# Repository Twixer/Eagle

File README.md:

Eagle projects
- Eagle-Tutorial-1-Files  : tutorial
- led-blink-relay : tutorial
- RFM12B : home automation
- TinyTx3 : home automation

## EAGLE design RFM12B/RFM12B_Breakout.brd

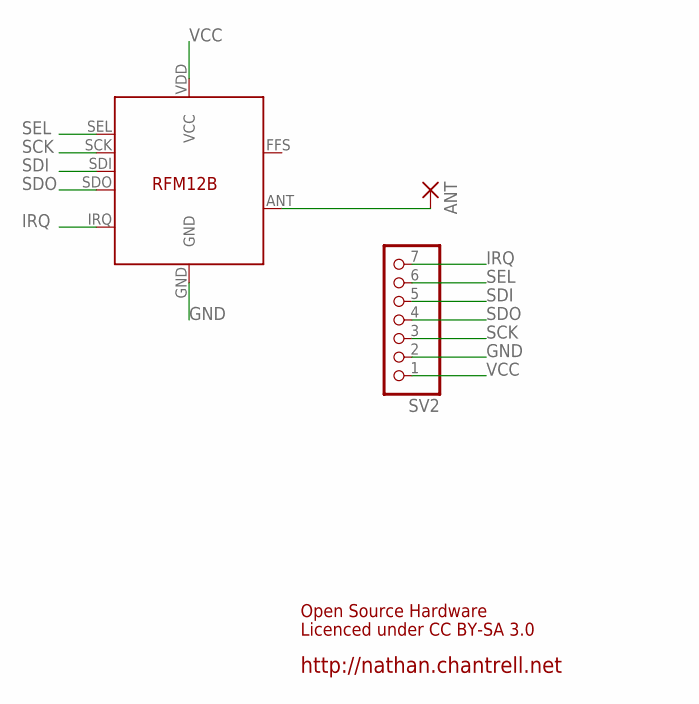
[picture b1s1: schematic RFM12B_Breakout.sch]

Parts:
ANT: 1,6/0,8
SV2: PINHD-1X7; 1X07
U$1: RFM12B

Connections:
GND: SV2.2, U$1.GND
IRQ: SV2.7, U$1.IRQ
unnamed: ANT.1, U$1.ANT
SCK: SV2.3, U$1.SCK
SDI: SV2.5, U$1.SDI
SDO: SV2.4, U$1.SDO
SEL: SV2.6, U$1.SEL
VCC: SV2.1, U$1.VDD (VCC)

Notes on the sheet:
http://nathan.chantrell.net
Open Source Hardware
Licenced under CC BY-SA 3.0

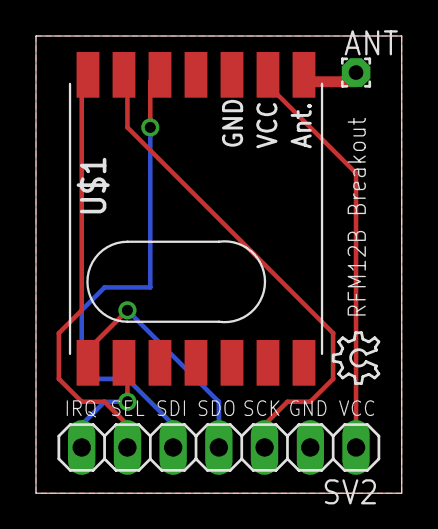
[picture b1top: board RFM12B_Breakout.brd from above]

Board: 2 copper layers, 20.3 x 25.4 mm, 4 parts (0 on the bottom side), 8 nets.

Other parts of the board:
U$4: OSHW_6X100_NOTEXT

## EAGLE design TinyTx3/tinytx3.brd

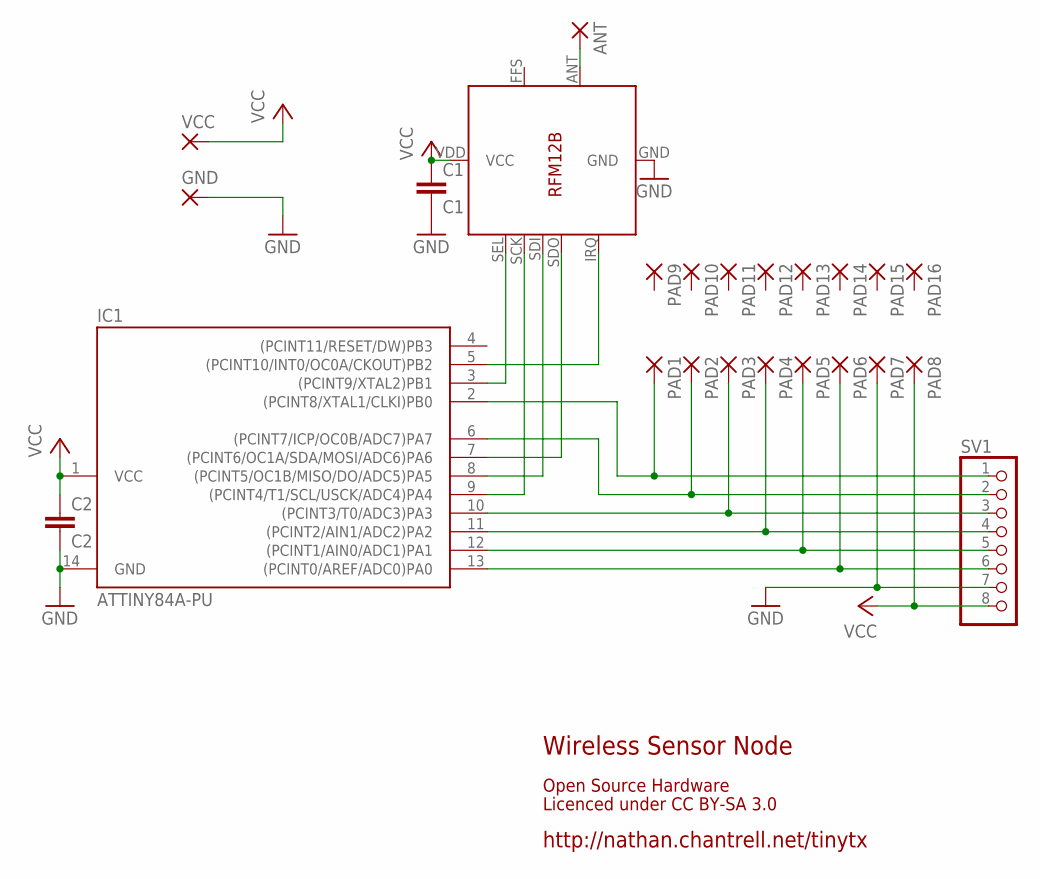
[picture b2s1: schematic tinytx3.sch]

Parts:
ANT: 1,6/0,8
C1: C1; C025-025X050
C2: C2; C025-025X050
GND: 2,15/1,0
IC1: ATTINY84A-PU; DIL14
PAD1, PAD2, PAD3, PAD4, PAD5, PAD6, PAD7, PAD8, PAD9, PAD10, PAD11, PAD12, PAD13, PAD14, PAD15, PAD16: 1,6/0,9
SV1: PINHD-1X8; 1X08
U$1: RFM12B
VCC: 2,15/1,0

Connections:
GND: C1.2, C2.2, GND.1, IC1.14 (GND), PAD7.1, SV1.7, U$1.GND
unnamed: IC1.3 ((PCINT9/XTAL2)PB1), U$1.SEL
unnamed: IC1.5 ((PCINT10/INT0/OC0A/CKOUT)PB2), U$1.IRQ
unnamed: IC1.8 ((PCINT5/OC1B/MISO/DO/ADC5)PA5), U$1.SDI
unnamed: IC1.7 ((PCINT6/OC1A/SDA/MOSI/ADC6)PA6), U$1.SDO
unnamed: ANT.1, U$1.ANT
unnamed: IC1.9 ((PCINT4/T1/SCL/USCK/ADC4)PA4), U$1.SCK
unnamed: IC1.6 ((PCINT7/ICP/OC0B/ADC7)PA7), PAD2.1, SV1.2
unnamed: IC1.13 ((PCINT0/AREF/ADC0)PA0), PAD6.1, SV1.6
unnamed: IC1.12 ((PCINT1/AIN0/ADC1)PA1), PAD5.1, SV1.5
unnamed: IC1.2 ((PCINT8/XTAL1/CLKI)PB0), PAD1.1, SV1.1
unnamed: IC1.11 ((PCINT2/AIN1/ADC2)PA2), PAD4.1, SV1.4
unnamed: IC1.10 ((PCINT3/T0/ADC3)PA3), PAD3.1, SV1.3
VCC: C1.1, C2.1, IC1.1 (VCC), PAD8.1, SV1.8, U$1.VDD (VCC), VCC.1

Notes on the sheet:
http://nathan.chantrell.net/tinytx
Wireless Sensor Node
Licenced under CC BY-SA 3.0
Open Source Hardware

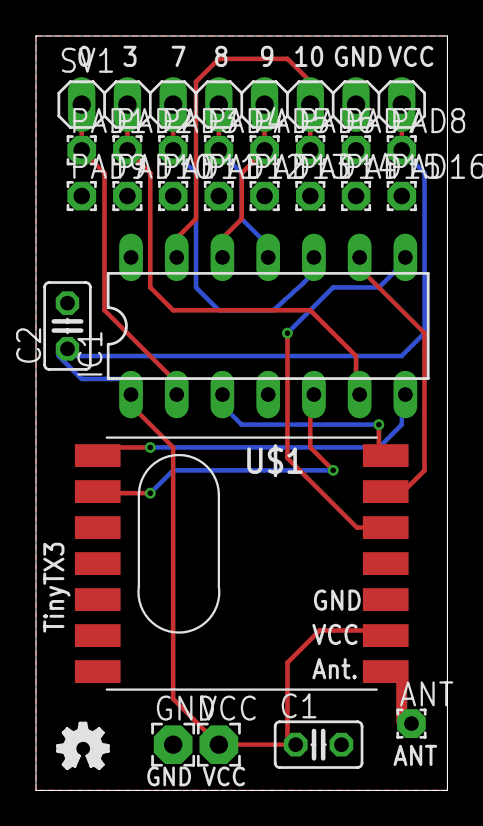
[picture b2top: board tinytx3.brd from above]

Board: 2 copper layers, 22.9 x 41.9 mm, 25 parts (0 on the bottom side), 14 nets.

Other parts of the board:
U$2: OSHW_FILLX100_NOTEXT

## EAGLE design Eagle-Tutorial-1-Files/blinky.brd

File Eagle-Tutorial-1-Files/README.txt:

Jeremy Blum's Eagle CAD Tutorial Series
=======================================
These files are meant to accompany Jeremy Blum's Eagle CAD Tutorial Series.  
These tutorials were sponsored by element14 (http://www.element14.com) with support from CadSoft (http://www.cadsoftusa.com)  
You can watch these tutorials on youtube or my website:  
>>YouTube				- http://www.youtube.com/playlist?list=PL868B73617C6F6FAD  
>>Jeremy's Website		- http://jeremyblum.com/category/eagle-tutorials/  

Open Source License
-------------------
These files are distributed under the GNU GPL Open Source License.  
Further information can be found in the LICENSE file.  

Learn More about Eagle
----------------------
If you need help with Eagle or want to learn more, I recommend these resources:  
>>element14 CadSoft Group	- http://www.element-14.com/cadsoft  
>>Eagle Guided Tour			- http://www.cadsoftusa.com/eagle-pcb-design-software/guided-tour/  
>>Sparkfun Eagle Tutorials	- http://www.sparkfun.com/tutorials/108  

Author Info
-----------
The Original author of these files is Jeremy Blum.  
He can be reached through his website, http://www.jeremyblum.com.  
NO WARRANTY is provided with these files, since they are released under the GNU GPL.  
Follow Jeremy on Twitter: http://www.twitter.com/sciguy14  
Subscribe to Jeremy on Youtube: http://www.youtube.com/subscription_center?add_user=sciguy14  
"Like" Jeremy on Facebook: http://www.facebook.com/JeremyTheEngineer

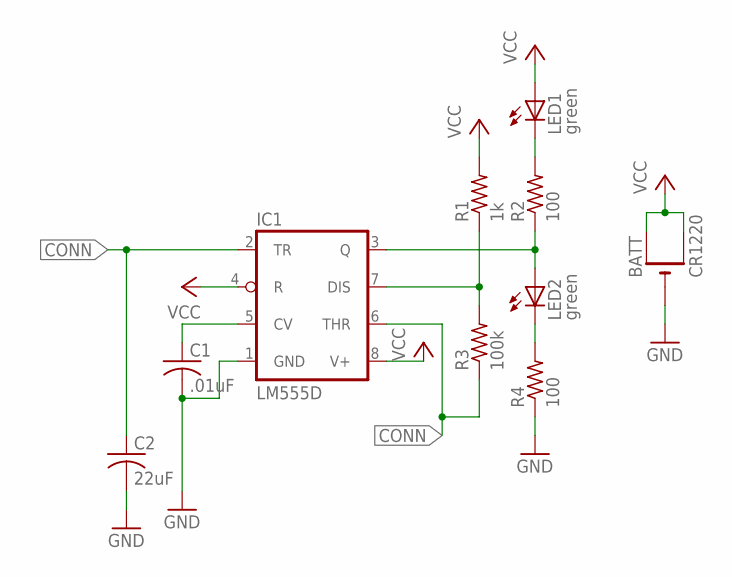
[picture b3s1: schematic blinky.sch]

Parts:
BATT: CR1220; CR1220-SMD
C1: .01uF; C0805
C2: 22uF; C0805
IC1: LM555D; SO08
LED1, LED2: green; CHIPLED_0805
R1: 1k; R0805
R2, R4: 100; R0805
R3: 100k; R0805

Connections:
CONN: C2.1, IC1.2 (TR), IC1.6 (THR), R3.1
GND: BATT.-, C1.2, C2.2, IC1.1 (GND), R4.1
unnamed: LED1.C, R2.2
unnamed: IC1.3 (Q), LED2.A, R2.1
unnamed: LED2.C, R4.2
unnamed: IC1.7 (DIS), R1.1, R3.2
unnamed: C1.1, IC1.5 (CV)
VCC: BATT.+$1 (+), BATT.+$2 (+1), IC1.4 (R), IC1.8 (V+), LED1.A, R1.2

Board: 2 copper layers, 10 parts (0 on the bottom side), 8 nets, no tracks yet.

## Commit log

2018-03-11 doc(readme) first commit
2018-03-11 feat(projects) add Eagle projects
2018-03-11 doc(sch) add a description frame
